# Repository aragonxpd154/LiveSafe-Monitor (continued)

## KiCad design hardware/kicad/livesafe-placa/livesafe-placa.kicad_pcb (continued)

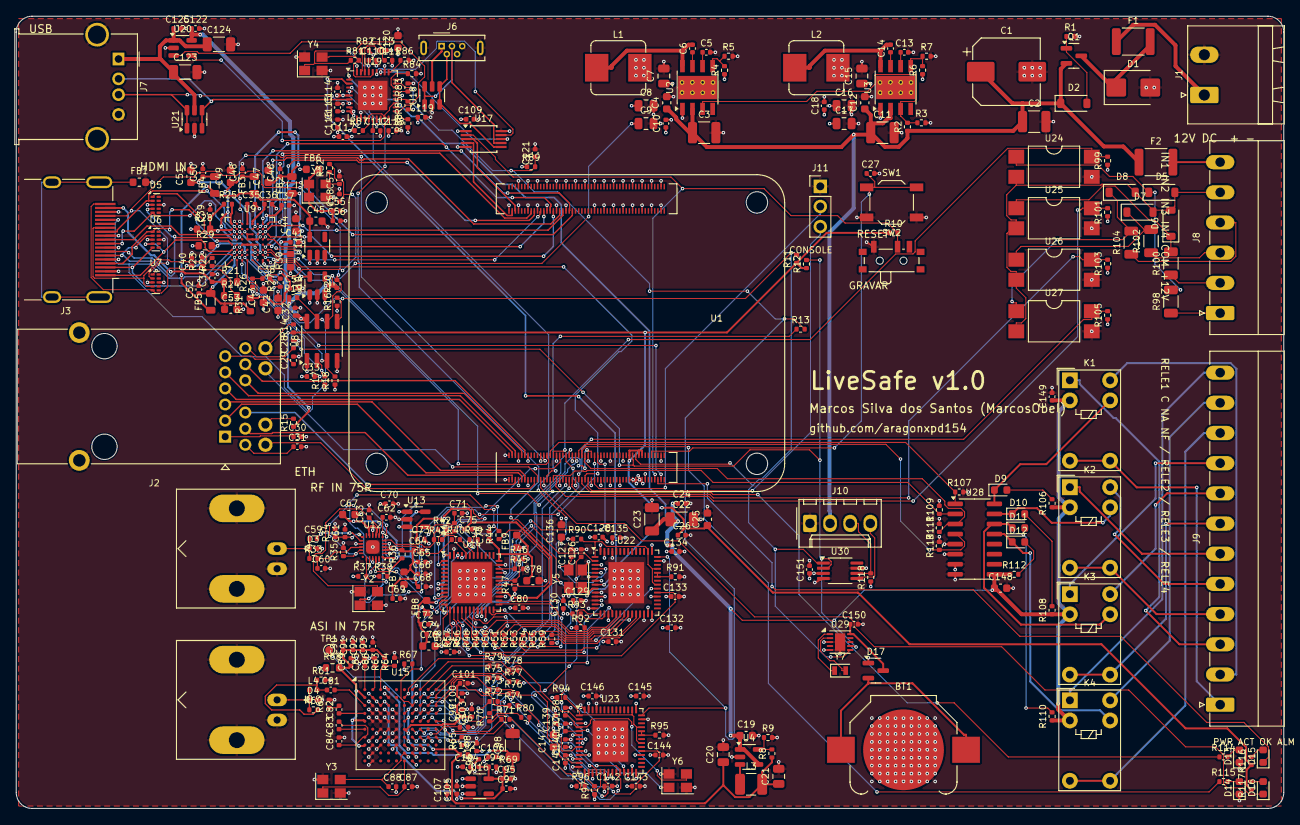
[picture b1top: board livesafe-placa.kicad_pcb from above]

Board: 4 copper layers, 160.0 x 100.0 mm, 358 parts (0 on the bottom side), 284 nets.

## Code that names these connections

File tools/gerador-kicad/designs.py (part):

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
Convenções de nomes de rede:
  +12V_IN  entrada bruta     +12V  depois da proteção     +5V, +3V3, +1V2  trilhos
  CM4_3V3  saída de 3,3 V do próprio CM4 (referência dos GPIO)
  *_N      sinal ativo em nível baixo
"""
import parts
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             'dtoverlay=tc358743-audio, dtparam=i2c_arm=on, dtparam=spi=on, dtoverlay=i2c-rtc,pcf85063a,i2c_csi_dsi',
             'Chave GRAVAR: leva nRPIBOOT a 0 e passa a USB do CM4 para o micro-USB interno (rpiboot / gravar o eMMC).'])
    b.group('Módulo')
    gpio = {'GPIO2': 'RF_SDA', 'GPIO3': 'RF_SCL', 'GPIO4': 'RF_RESET_N', 'GPIO5': 'ASI_RESET_N', 'GPIO6': 'GPI1',
            'GPIO12': 'GPI2', 'GPIO25': 'GPI3', 'GPIO24': 'GPI4', 'GPIO13': 'GPO1', 'GPIO16': 'GPO2', 'GPIO17': 'GPO3',
            'GPIO22': 'GPO4', 'GPIO23': 'LED_OK', 'GPIO27': 'LED_ALM', 'GPIO14': 'CON_TX', 'GPIO15': 'CON_RX',
            'GPIO18': 'I2S_BCK', 'GPIO19': 'I2S_LRCK', 'GPIO20': 'I2S_DIN', 'GPIO26': 'HDMI_INT', 'GPIO8': 'ASI_CS_N',
            'GPIO9': 'ASI_MISO', 'GPIO10': 'ASI_MOSI', 'GPIO11': 'ASI_SCK', 'GPIO7': 'ASI_LOCK', 'GPIO21': 'USB_RST_GPIO'}
    nets = {'+5V_IN': '+5V', 'GND': 'GND', 'GPIO_VREF': 'CM4_3V3', '+3V3_OUT': 'CM4_3V3', 'RUN_PG': 'CM4_RUN',
            'nRPIBOOT': 'BOOT_N', 'nPI_LED_PWR': 'LED_PWR_N', 'PI_nLED_Activity': 'LED_ACT_N', 'SCL0': 'I2C0_SCL',
            'SDA0': 'I2C0_SDA', 'Camera_GPIO': 'CAM_GPIO', 'USB2_P': 'USB_CM4_P', 'USB2_N': 'USB_CM4_N',
            'USB_OTG_ID': 'GND', 'ETH_nLED1': 'ETH_nLED1', 'ETH_nLED2': 'ETH_nLED2',
            'CAM1_C_P': 'CSI_C_P', 'CAM1_C_N': 'CSI_C_N'}
    for i in range(4):
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    b.C('100nF', 'CM4_RUN', 'GND', mpn=CAPS[('100nF', '0402')])
    b.R('4.7k', 'CM4_3V3', 'I2C0_SDA')
    b.R('4.7k', 'CM4_3V3', 'I2C0_SCL')
    b.R('1k', 'USB_RST_GPIO', 'USB_RST_N')


# =============================================================================
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        b.C('100nF', n, 'GND', mpn=CAPS[('100nF', '0402')])
    b.R('10k', '+3V3', 'HDMI_RESET_N')
    b.C('100nF', 'HDMI_RESET_N', 'GND', mpn=CAPS[('100nF', '0402')])
    b.R('0', 'CAM_GPIO', 'HDMI_RESET_N', dnp=True, note='reset por software (opcional)')
    b.group('Alimentação da ponte')
    for n in ('TC_AVDD33', 'TC_VDDIO1', 'TC_VDDIO2'):
        b.R('0', '+3V3', n, '0603')
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    b.R('0', 'TUN_LIF_P', 'DEM_ADC_P', note='pode virar capacitor de acoplamento')
    b.R('0', 'TUN_LIF_N', 'DEM_ADC_N', note='pode virar capacitor de acoplamento')
    b.R('0', 'TUN_XOUT', 'DEM_CLKIN')
    b.R('0', 'TUN_XOUT', 'DEM_XTALI', dnp=True, note='clock pelo pino 33 (CLK_XTAL_IN)')
    b.R('0', 'DEM_MPA', 'TUN_AGC1')
    b.R('0', 'DEM_MPD', 'TUN_AGC2', dnp=True, note='AGC pelo MP_D (opção)')
    b.C('10nF', 'TUN_AGC1', 'GND', dnp=True, note='filtro RC do AGC (opção)')
    b.group('Demodulador Si2183-B60')
    dem = {'TC_ADC_P': 'DEM_ADC_P', 'TC_ADC_N': 'DEM_ADC_N', 'CLK_IN_OUT': 'DEM_CLKIN', 'XTAL_I/CLK_IN': 'DEM_XTALI',
           'SDA_HOST': 'RF_SDA', 'SCL_HOST': 'RF_SCL', 'ADDR': 'DEM_ADDR', 'RESETB': 'RF_RESET_N',
           'TS_CLK': 'DEM_TSCLK', 'TS_SYNC': 'DEM_TSSYNC', 'TS_VAL': 'DEM_TSVAL', 'TS_ERR/GPIO_1': 'DEM_TSERR',
           'SDA_MAST': 'TUN_SDA', 'SCL_MAST': 'TUN_SCL', 'MP_A': 'DEM_MPA', 'MP_D': 'DEM_MPD',
           'VDD_VCORE': 'DEM_VCORE', 'VDD_VANA': 'DEM_VANA', 'VDD_VIO': '+3V3', 'GND': 'GND',
           'TS_DATA0/TS_SER': 'DEM_TSD0'}
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    b.C('16pF', 'ASI_X1', 'GND', mpn='0402CG160J500NT', fab='FH')
    b.C('16pF', 'ASI_X2', 'GND', mpn='0402CG160J500NT', fab='FH')
    b.two('TP', 'XTAL_OUT', 'ASI_XOUT', None, 'TP')
    b.comps[list(b.comps)[-1]].pins = {'1': 'ASI_XOUT'}
    b.R('10k', '+3V3', 'ASI_DVBASI')
    b.R('10k', 'ASI_SMPTE_BYP', 'GND')
    b.R('10k', '+3V3', 'ASI_RESET_N')
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            'vai ao micro-USB interno de serviço. O hub atende a FX2LP #1 (TS do demodulador), a FX2LP #2 (bytes ASI) e a '
            'porta USB-A; a porta 4 fica desligada por strap.',
            ['FX2LP sem EEPROM: o firmware é carregado pelo Linux a cada partida (fxload / libusb).',
             'USB_RST_N reinicia o hub e as duas FX2LP (RC de 10 ms + GPIO21 do CM4, para recuperação por software).'])
    b.group('Chave USB e porta de serviço (interna)')
    b.part('FSUSB42MX', 'FSUSB42MUX', {'VCC': '+3V3', 'GND': 'GND', 'D+': 'USB_CM4_P', 'D-': 'USB_CM4_N',
                                       'SEL': 'BOOT_N', 'OE_N': 'GND', 'HSD1+': 'USB_SERV_P', 'HSD1-': 'USB_SERV_N',
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                                   'SHIELD': 'GND'}, ref='J7')
    b.part('USBLC6-2SC6', 'USBLC6-2SC6', {'IO1a': 'USB_A_P', 'IO1b': 'USB_A_P', 'IO2a': 'USB_A_N',
                                          'IO2b': 'USB_A_N', 'VBUS': 'USB_A_VBUS', 'GND': 'GND'})
    for k, ts, slwr, pa0, pa1 in ((1, 'TS1', 'TS1_VAL', 'TS1_SYNC', 'TS1_ERR'), (2, 'TS2', 'TS2_SYNC', 'TS2_WERR', None)):
        b.group(f'Ponte FX2LP #{k} ({"TS do demodulador" if k == 1 else "bytes ASI"})')
        fx = {'D+': f'USB_FX{k}_P', 'D-': f'USB_FX{k}_N', 'XTALIN': f'FX{k}_XI', 'XTALOUT': f'FX{k}_XO',
              'RESETN': 'USB_RST_N', 'WAKEUP': f'FX{k}_PU', 'SCL': f'FX{k}_SCL', 'SDA': f'FX{k}_SDA',
              'RESERVED': 'GND', 'IFCLK': f'{ts}_CLK', 'RDY1/SLWR': slwr, 'RDY0/SLRD': f'FX{k}_PU',
              'PA0/INT0': pa0, 'PA1/INT1': pa1, 'PA2/SLOE': f'FX{k}_PU', 'PA4/FIFOADR0': f'FX{k}_PD',
              'PA5/FIFOADR1': f'FX{k}_PD', 'PA6/PKTEND': f'FX{k}_PU', 'VCC': '+3V3', 'AVCC': '+3V3',
              'GND': 'GND', 'AGND': 'GND'}
        for i in range(8):
            fx[f'PB{i}/FD{i}'] = f'{ts}_D{i}'
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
